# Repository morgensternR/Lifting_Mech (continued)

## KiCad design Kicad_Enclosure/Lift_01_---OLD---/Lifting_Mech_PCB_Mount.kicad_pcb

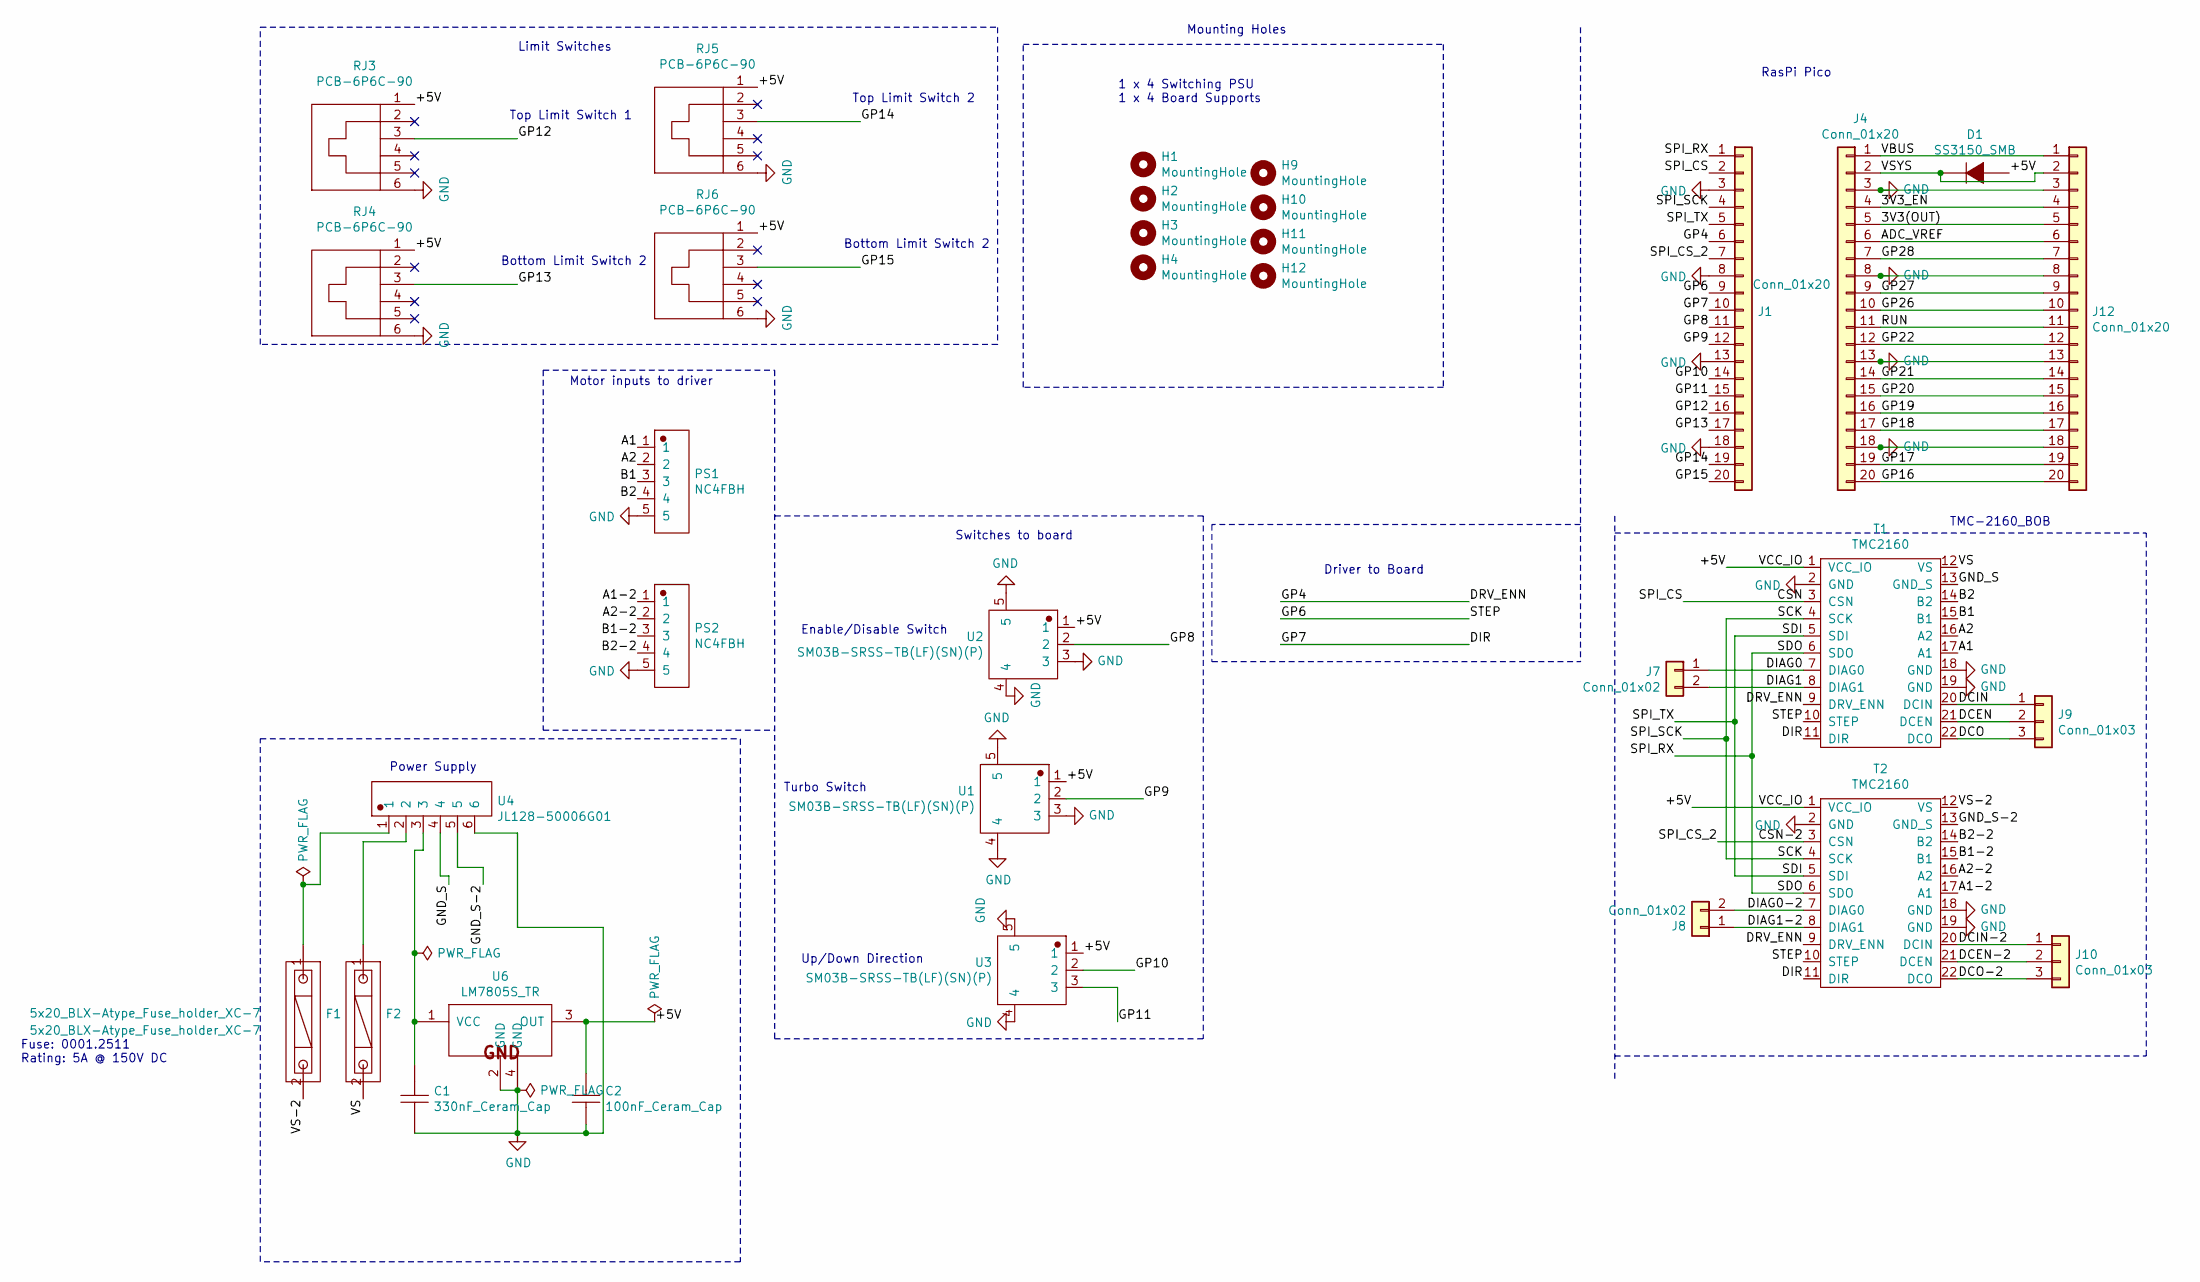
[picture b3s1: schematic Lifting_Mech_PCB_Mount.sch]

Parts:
C1: 330nF_Ceram_Cap; C1206-330nF; LCSC C710478
C2: 100nF_Ceram_Cap; C0805-100nF; LCSC C28233
D1: SS3150_SMB; SMB_L4.6-W3.6_Schottky; LCSC C47124
F1, F2: 5x20_BLX-Atype_Fuse_holder_XC-7; FUSE-TH_L22.6-W9.0; LCSC C3131
H1, H2, H3, H4: MountingHole; MountingHole_5.3mm_M5_DIN965_Pad
H9, H10, H11, H12: MountingHole; MountingHole_3.2mm_M3_DIN965_Pad
J1, J4, J12: Conn_01x20; PinSocket_1x20_P2.54mm_Vertical; LCSC C2833318
J7, J8: Conn_01x02; PinSocket_1x02_P2.54mm_Vertical
J9, J10: Conn_01x03; PinSocket_1x03_P2.54mm_Vertical
PS1, PS2: NC4FBH; CONN-TH_NC4FBH_XLR4_Female_RA_Panel; LCSC std:240b847a4e2e4ed7980c8865ae95f7a5
RJ3, RJ4, RJ5, RJ6: PCB-6P6C-90; RJ11-TH_PCB-6P6C-90; LCSC C189750
T1, T2: TMC2160; TMC_2160
U1, U2, U3: SM03B-SRSS-TB(LF)(SN)(P); CONN-SMD_SM03B-SRSS-TB-LF-SN-P; LCSC C160403
U4: JL128-50006G01; CONN-TH_JL128-50006G01_6_Screw; LCSC C2802630
U6: LM7805S_TR; TO-263-3_L8.6-W10.2-P2.54-LS14.4-BR; LCSC C507146

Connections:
/3V3(OUT): J4.5, J12.5
/3V3_EN: J4.4, J12.4
/+5V: C2.1, D1.1 (A), RJ3.1, RJ4.1, RJ5.1, RJ6.1, T1.1 (VCC_IO), T2.1 (VCC_IO), U1.1, U2.1, U3.1, U6.3 (OUT)
/A1: PS1.1, T1.17 (A1)
/A1-2: PS2.1, T2.17 (A1)
/A2: PS1.2, T1.16 (A2)
/A2-2: PS2.2, T2.16 (A2)
/ADC_VREF: J4.6, J12.6
/B1: PS1.3, T1.15 (B1)
/B1-2: PS2.3, T2.15 (B1)
/B2: PS1.4, T1.14 (B2)
/B2-2: PS2.4, T2.14 (B2)
/CSN: J1.2, T1.3 (CSN)
/CSN-2: J1.7, T2.3 (CSN)
/DCEN: J9.2, T1.21 (DCEN)
/DCEN-2: J10.2, T2.21 (DCEN)
/DCIN: J9.1, T1.20 (DCIN)
/DCIN-2: J10.1, T2.20 (DCIN)
/DCO: J9.3, T1.22 (DCO)
/DCO-2: J10.3, T2.22 (DCO)
/DIAG0: J7.1, T1.7 (DIAG0)
/DIAG0-2: J8.2, T2.7 (DIAG0)
/DIAG1: J7.2, T1.8 (DIAG1)
/DIAG1-2: J8.1, T2.8 (DIAG1)
/DIR: J1.10, T1.11 (DIR), T2.11 (DIR)
/DRV_ENN: J1.6, T1.9 (DRV_ENN), T2.9 (DRV_ENN)
/GND_S: T1.13 (GND_S), U4.4
/GND_S-2: T2.13 (GND_S), U4.5
/GP6: J1.9, T1.10 (STEP), T2.10 (STEP)
/GP8: J1.11, U2.2
/GP9: J1.12, U1.2
/GP10: J1.14, U3.2
/GP11: J1.15, U3.3
/GP12: J1.16, RJ3.3
/GP13: J1.17, RJ4.3
/GP14: J1.19, RJ5.3
/GP15: J1.20, RJ6.3
/GP16: J4.20, J12.20
/GP17: J4.19, J12.19
/GP18: J4.17, J12.17
/GP19: J4.16, J12.16
/GP20: J4.15, J12.15
/GP21: J4.14, J12.14
/GP22: J4.12, J12.12
/GP26: J4.10, J12.10
/GP27: J4.9, J12.9
/GP28: J4.7, J12.7
/RUN: J4.11, J12.11
/SCK: J1.4, T1.4 (SCK), T2.4 (SCK)
/SDI: J1.5, T1.5 (SDI), T2.5 (SDI)
/SDO: J1.1, T1.6 (SDO), T2.6 (SDO)
/VBUS: J4.1, J12.1
/VS: F2.2, T1.12 (VS)
/VS-2: F1.2, T2.12 (VS)
/VSYS: D1.2 (K), J4.2, J12.2
GND: C1.2, C2.2, J1.3, J1.8, J1.13, J1.18, J4.3, J4.8, J4.13, J4.18, J12.3, J12.8, J12.13, J12.18, PS1.5, PS2.5, RJ3.6, RJ4.6, RJ5.6, RJ6.6, T1.2 (GND), T1.18 (GND), T1.19 (GND), T2.2 (GND), T2.18 (GND), T2.19 (GND), U1.3, U1.4, U1.5, U2.3, U2.4, U2.5, U3.4, U3.5, U4.6, U6.2 (GND), U6.4 (GND)
unnamed: C1.1, U4.3, U6.1 (VCC)
unnamed: F1.1, U4.1
unnamed: F2.1, U4.2

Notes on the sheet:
Enable/Disable Switch
Up/Down Direction
Driver to Board
Mounting Holes
Limit Switches
Top Limit Switch 1
Bottom Limit Switch 2
Top Limit Switch 2
Motor inputs to driver
TMC-2160_BOB
Turbo Switch
Switches to board
Power Supply
1 x 4 Switching PSU 1 x 4 Board Supports
RasPi Pico
Fuse: 0001.2511 Rating: 5A @ 150V DC

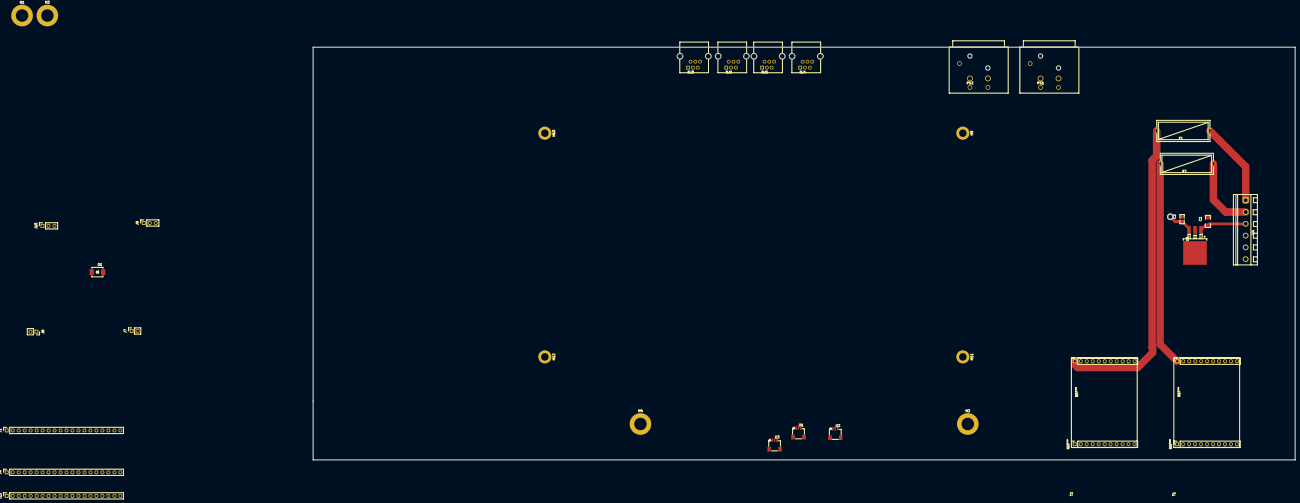
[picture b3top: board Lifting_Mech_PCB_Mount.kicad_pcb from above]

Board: 2 copper layers, 417.0 x 175.2 mm, 33 parts (0 on the bottom side), 59 nets.

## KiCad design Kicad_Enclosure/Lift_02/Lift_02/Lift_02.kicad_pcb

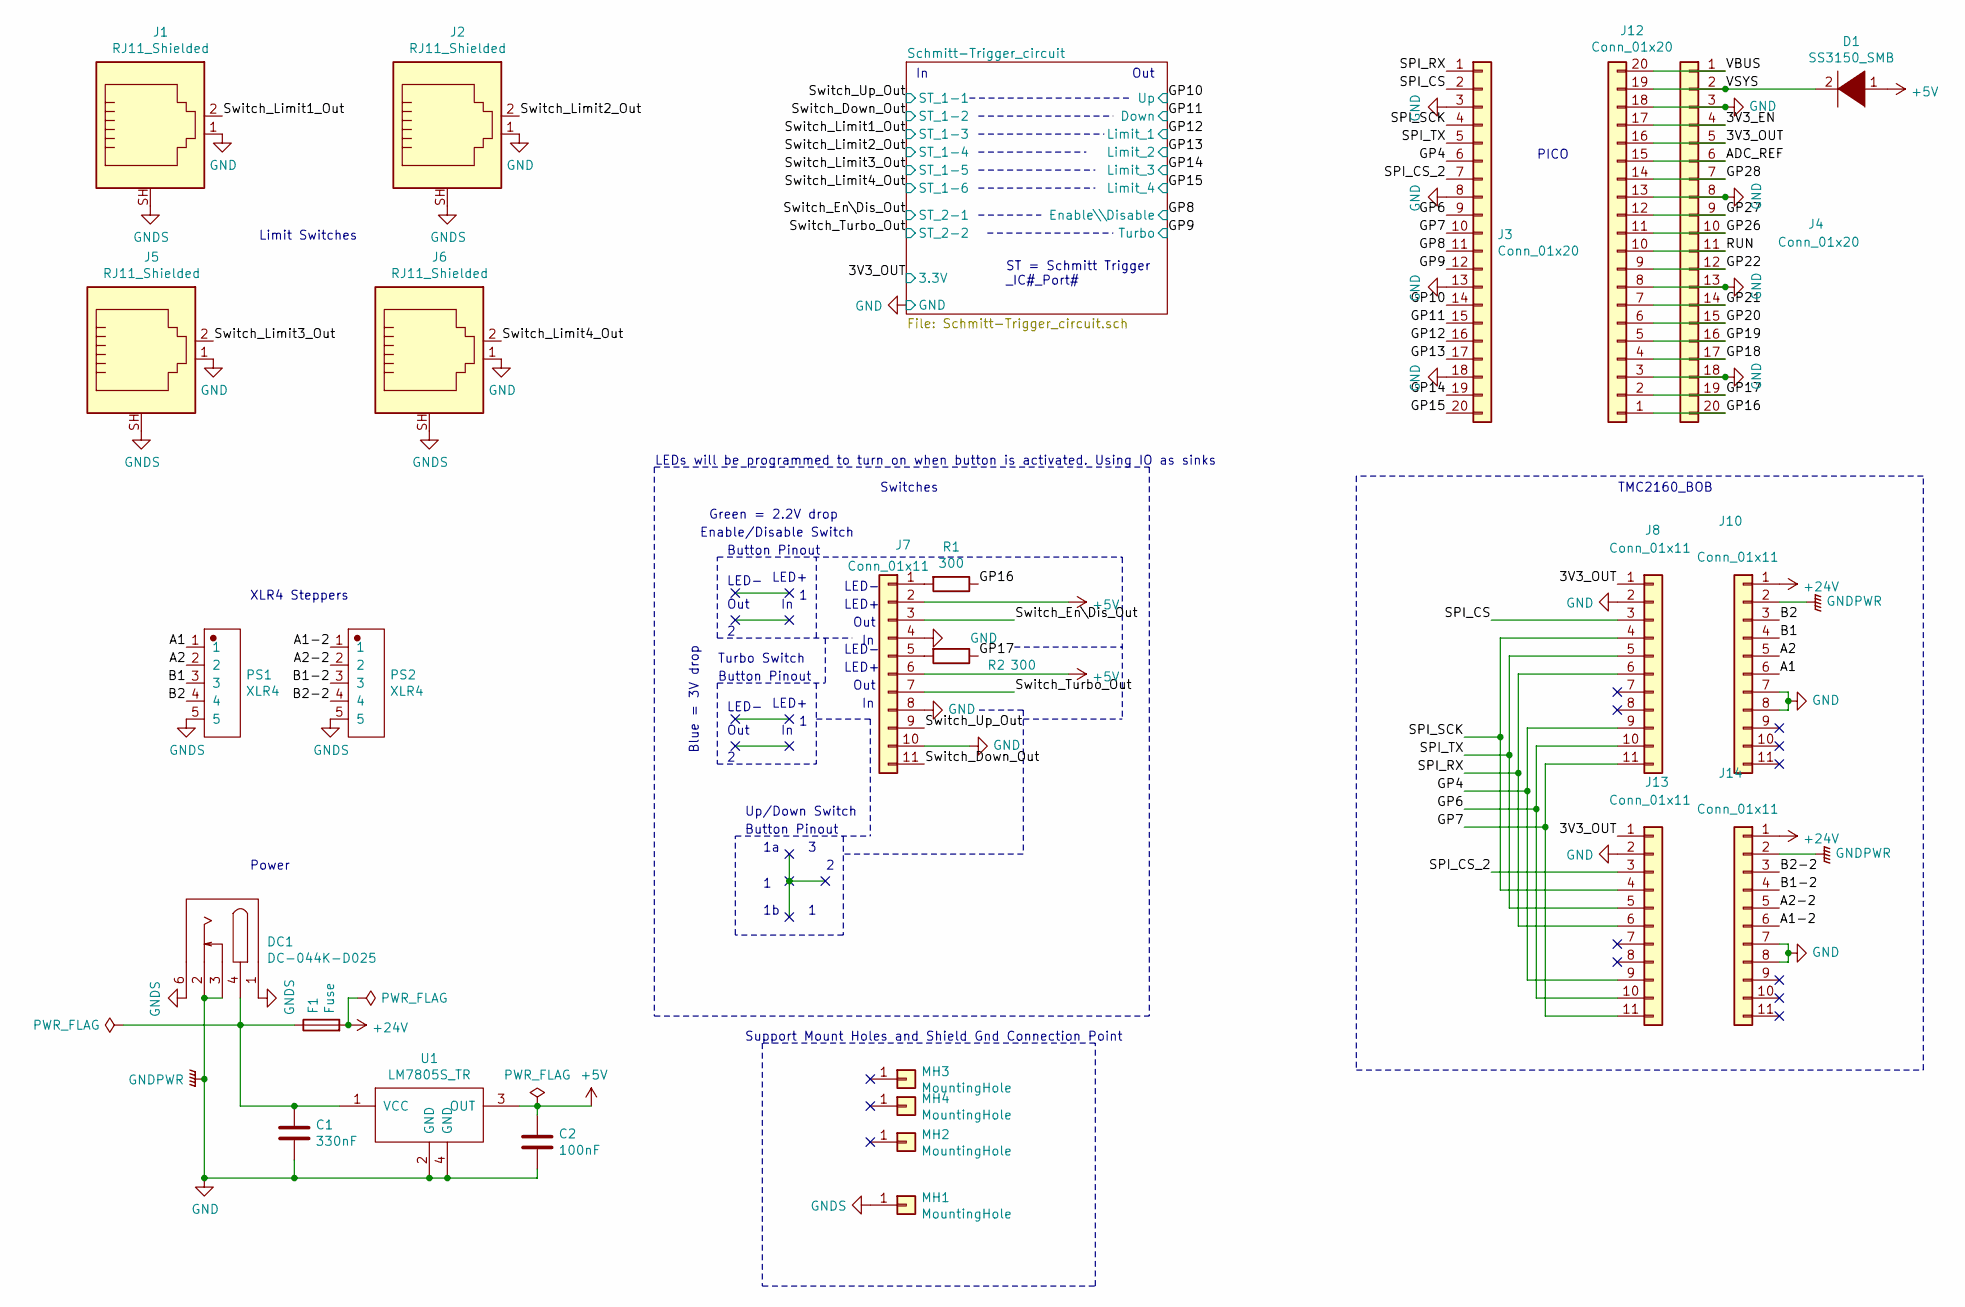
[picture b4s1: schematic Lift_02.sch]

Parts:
C1: 330nF; C_1206_3216Metric_Pad1.33x1.80mm_HandSolder; LCSC C710478
C2: 100nF; C_0805_2012Metric_Pad1.18x1.45mm_HandSolder; LCSC C28233
D1: SS3150_SMB; SMB_L4.6-W3.6-LS5.3-R-RD; LCSC C47124
DC1: DC-044K-D025; DC-IN-TH_DC-044K-D025; LCSC C963204
F1: Fuse; FUSE-TH_L22.6-W9.0; LCSC C3131
J1, J2, J5, J6: RJ11_Shielded; RJ11-TH_PCB-6P6C-90; LCSC C189750
J3, J4: Conn_01x20; PinSocket_1x20_P2.54mm_Vertical; LCSC C50984
J7: Conn_01x11; CONN-TH_B11B-ZR-LF-SN; LCSC C160345
J8, J10, J13, J14: Conn_01x11; PinSocket_1x11_P2.54mm_Vertical; LCSC C2897374
J12: Conn_01x20; PinHeader_1x20_P2.54mm_Vertical
MH1: MountingHole; MountingHole_5.3mm_M5_DIN965_Pad
MH2, MH3, MH4: MountingHole; MountingHole_5.3mm_M5
PS1, PS2: XLR4; CONN-TH_NC4FBH; LCSC C368478
R1, R2: 300; R_0805_2012Metric_Pad1.20x1.40mm_HandSolder; LCSC C17617
U1: LM7805S_TR; TO-263-3_L8.6-W10.2-P2.54-LS14.4-BR; LCSC C507146

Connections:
+5V: C2.1, D1.1 (K), J7.2, J7.6, U1.3 (OUT)
+24V: F1.2, J10.1, J14.1
/3V3_EN: J4.4, J12.17
/3V3_OUT: J4.5, J8.1, J12.16, J13.1; also elsewhere on the board
/A1: J10.6, PS1.1
/A1-2: J14.6, PS2.1
/A2: J10.5, PS1.2
/A2-2: J14.5, PS2.2
/ADC_REF: J4.6, J12.15
/B1: J10.4, PS1.3
/B1-2: J14.4, PS2.3
/B2: J10.3, PS1.4
/B2-2: J14.3, PS2.4
/GP4: J3.6, J8.9, J13.9
/GP6: J3.9, J8.10, J13.10
/GP7: J3.10, J8.11, J13.11
/GP8: J3.11; also elsewhere on the board
/GP9: J3.12; also elsewhere on the board
/GP10: J3.14; also elsewhere on the board
/GP11: J3.15; also elsewhere on the board
/GP12: J3.16; also elsewhere on the board
/GP13: J3.17; also elsewhere on the board
/GP14: J3.19; also elsewhere on the board
/GP15: J3.20; also elsewhere on the board
/GP16: J4.20, J12.1, R1.1
/GP17: J4.19, J12.2, R2.1
/GP18: J4.17, J12.4
/GP19: J4.16, J12.5
/GP20: J4.15, J12.6
/GP21: J4.14, J12.7
/GP22: J4.12, J12.9
/GP26: J4.10, J12.11
/GP27: J4.9, J12.12
/GP28: J4.7, J12.14
/RUN: J4.11, J12.10
/SPI_CS: J3.2, J8.3
/SPI_CS_2: J3.7, J13.3
/SPI_RX: J3.1, J8.6, J13.6
/SPI_SCK: J3.4, J8.4, J13.4
/SPI_TX: J3.5, J8.5, J13.5
/Switch_Down_Out: J7.11; also elsewhere on the board
/Switch_En\Dis_Out: J7.3; also elsewhere on the board
/Switch_Limit1_Out: J1.2; also elsewhere on the board
/Switch_Limit2_Out: J2.2; also elsewhere on the board
/Switch_Limit3_Out: J5.2; also elsewhere on the board
/Switch_Limit4_Out: J6.2; also elsewhere on the board
/Switch_Turbo_Out: J7.7; also elsewhere on the board
/Switch_Up_Out: J7.9; also elsewhere on the board
/VBUS: J4.1, J12.20
/VSYS: D1.2 (A), J4.2, J12.19
GND: C1.2, C2.2, DC1.2, DC1.3, J1.1, J2.1, J3.3, J3.8, J3.13, J3.18, J4.3, J4.8, J4.13, J4.18, J5.1, J6.1, J7.4, J7.8, J7.10, J8.2, J10.2, J10.7, J10.8, J12.3, J12.8, J12.13, J12.18, J13.2, J14.2, J14.7, J14.8, U1.2 (GND), U1.4 (GND); also elsewhere on the board
GNDS: DC1.1, DC1.6, J1.SH, J2.SH, J5.SH, J6.SH, MH1.1, PS1.5, PS2.5
unnamed: C1.1, DC1.4, F1.1, U1.1 (VCC)
unnamed: J7.1, R1.2
unnamed: J7.5, R2.2

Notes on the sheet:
Up/Down Switch
Enable/Disable Switch
LED+
LED-
Out
Button Pinout
Switches
Out
LED+
LED-
Turbo Switch
LEDs will be programmed to turn on when button is activated. Using IO as sinks
XLR4 Steppers
Power
Limit Switches
PICO
Support Mount Holes and Shield Gnd Connection Point
TMC2160_BOB
ST = Schmitt Trigger _IC#_Port#
Blue = 3V drop
Green = 2.2V drop

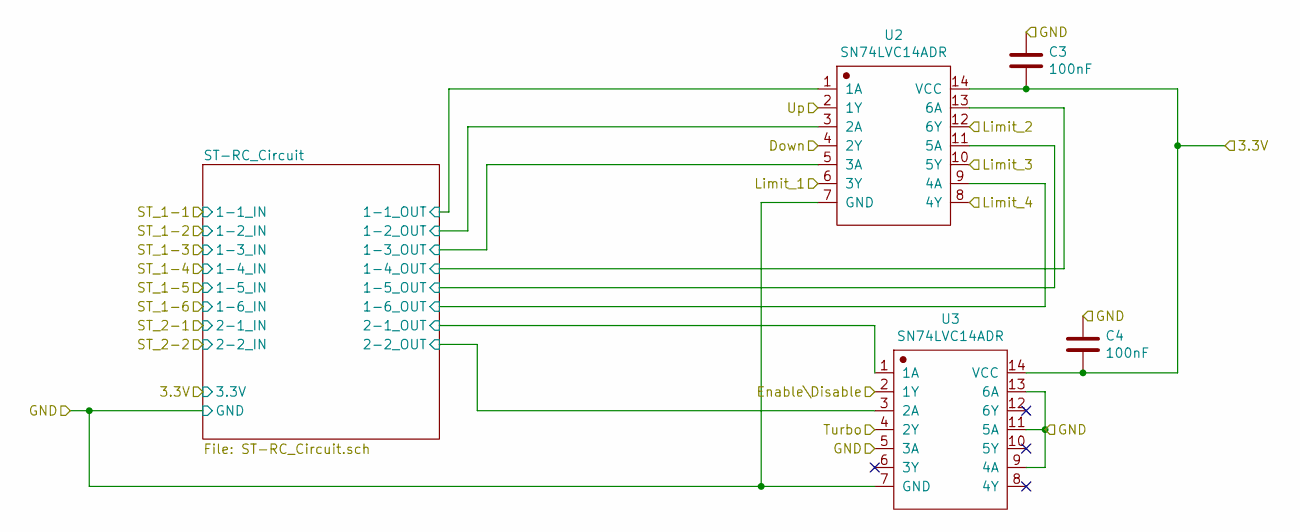
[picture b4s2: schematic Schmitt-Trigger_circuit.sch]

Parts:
C3, C4: 100nF; C_0603_1608Metric_Pad1.08x0.95mm_HandSolder; LCSC C14663
U2, U3: SN74LVC14ADR; SOIC-14_3.9x8.7mm_P1.27mm; LCSC C133541

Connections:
/3V3_OUT: C3.2, C4.2, U2.14 (VCC), U3.14 (VCC); also elsewhere on the board
/GP8: U3.2 (1Y); also elsewhere on the board
/GP9: U3.4 (2Y); also elsewhere on the board
/GP10: U2.2 (1Y); also elsewhere on the board
/GP11: U2.4 (2Y); also elsewhere on the board
/GP12: U2.6 (3Y); also elsewhere on the board
/GP13: U2.12 (6Y); also elsewhere on the board
/GP14: U2.10 (5Y); also elsewhere on the board
/GP15: U2.8 (4Y); also elsewhere on the board
/Schmitt-Trigger_circuit/ST-RC_Circuit/1-1_OUT: U2.1 (1A); also elsewhere on the board
/Schmitt-Trigger_circuit/ST-RC_Circuit/1-2_OUT: U2.3 (2A); also elsewhere on the board
/Schmitt-Trigger_circuit/ST-RC_Circuit/1-3_OUT: U2.5 (3A); also elsewhere on the board
/Schmitt-Trigger_circuit/ST-RC_Circuit/1-4_OUT: U2.13 (6A); also elsewhere on the board
/Schmitt-Trigger_circuit/ST-RC_Circuit/1-5_OUT: U2.11 (5A); also elsewhere on the board
/Schmitt-Trigger_circuit/ST-RC_Circuit/1-6_OUT: U2.9 (4A); also elsewhere on the board
/Schmitt-Trigger_circuit/ST-RC_Circuit/2-1_OUT: U3.1 (1A); also elsewhere on the board
/Schmitt-Trigger_circuit/ST-RC_Circuit/2-2_OUT: U3.3 (2A); also elsewhere on the board
GND: C3.1, C4.1, U2.7 (GND), U3.5 (3A), U3.7 (GND), U3.9 (4A), U3.11 (5A), U3.13 (6A); also elsewhere on the board

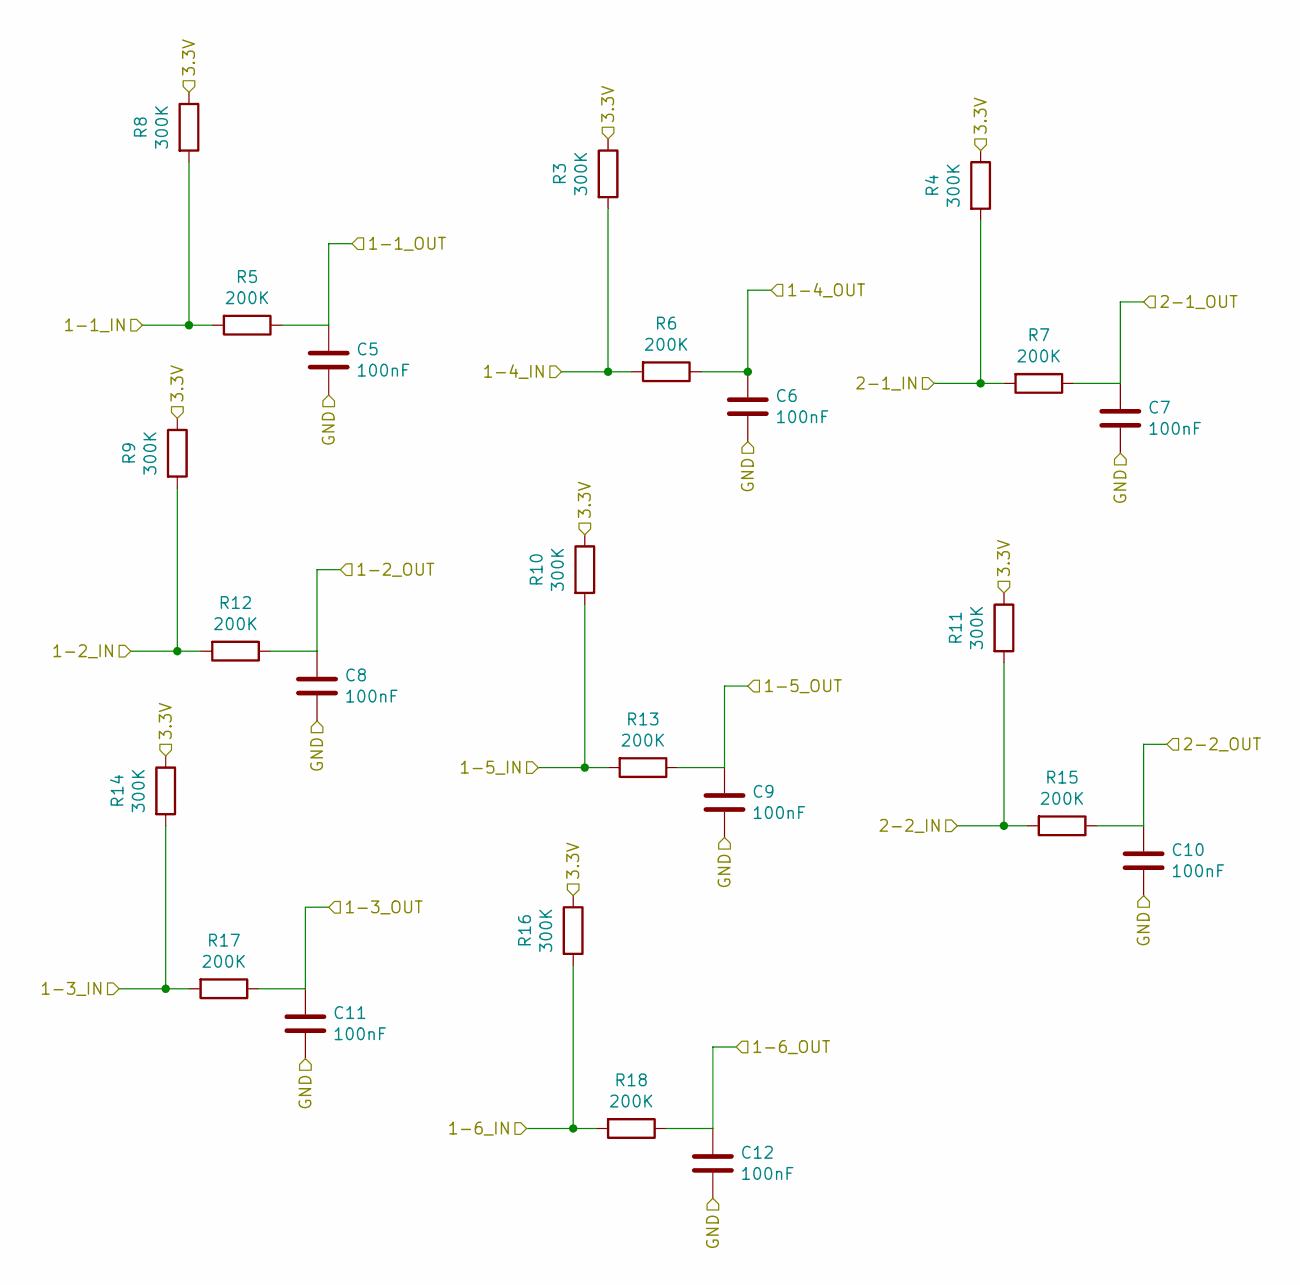
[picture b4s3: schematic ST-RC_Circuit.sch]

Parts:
C5, C6, C7, C8, C9, C10, C11, C12: 100nF; C_0603_1608Metric_Pad1.08x0.95mm_HandSolder; LCSC C14663
R3, R4, R8, R9, R10, R11, R14, R16: 300K; R_0603_1608Metric_Pad0.98x0.95mm_HandSolder; LCSC C23024
R5, R6, R7, R12, R13, R15, R17, R18: 200K; R_0603_1608Metric_Pad0.98x0.95mm_HandSolder; LCSC C25811

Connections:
/3V3_OUT: R3.1, R4.1, R8.1, R9.1, R10.1, R11.1, R14.1, R16.1; also elsewhere on the board
/Schmitt-Trigger_circuit/ST-RC_Circuit/1-1_OUT: C5.1, R5.1; also elsewhere on the board
/Schmitt-Trigger_circuit/ST-RC_Circuit/1-2_OUT: C8.1, R12.1; also elsewhere on the board
/Schmitt-Trigger_circuit/ST-RC_Circuit/1-3_OUT: C11.1, R17.1; also elsewhere on the board
/Schmitt-Trigger_circuit/ST-RC_Circuit/1-4_OUT: C6.1, R6.1; also elsewhere on the board
/Schmitt-Trigger_circuit/ST-RC_Circuit/1-5_OUT: C9.1, R13.1; also elsewhere on the board
/Schmitt-Trigger_circuit/ST-RC_Circuit/1-6_OUT: C12.1, R18.1; also elsewhere on the board
/Schmitt-Trigger_circuit/ST-RC_Circuit/2-1_OUT: C7.1, R7.1; also elsewhere on the board
/Schmitt-Trigger_circuit/ST-RC_Circuit/2-2_OUT: C10.1, R15.1; also elsewhere on the board
/Switch_Down_Out: R9.2, R12.2; also elsewhere on the board
/Switch_En\Dis_Out: R4.2, R7.2; also elsewhere on the board
/Switch_Limit1_Out: R14.2, R17.2; also elsewhere on the board
/Switch_Limit2_Out: R3.2, R6.2; also elsewhere on the board
/Switch_Limit3_Out: R10.2, R13.2; also elsewhere on the board
/Switch_Limit4_Out: R16.2, R18.2; also elsewhere on the board
/Switch_Turbo_Out: R11.2, R15.2; also elsewhere on the board
/Switch_Up_Out: R5.2, R8.2; also elsewhere on the board
GND: C5.2, C6.2, C7.2, C8.2, C9.2, C10.2, C11.2, C12.2; also elsewhere on the board

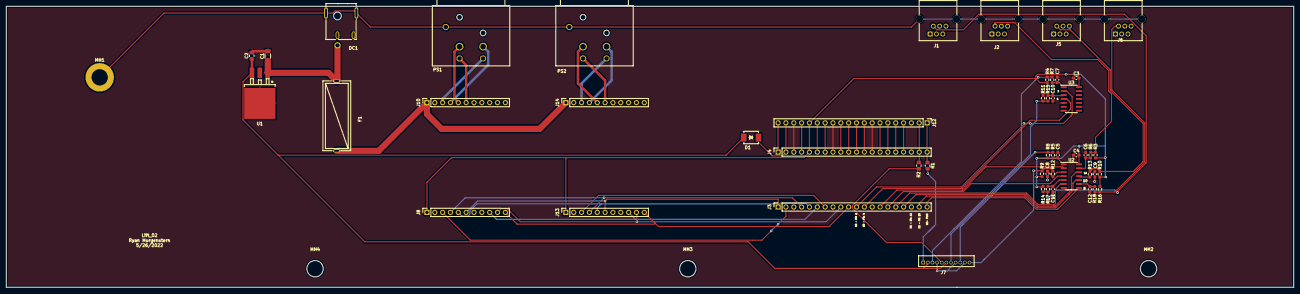
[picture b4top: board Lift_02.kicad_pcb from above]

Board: 2 copper layers, 417.0 x 91.0 mm, 54 parts (0 on the bottom side), 63 nets.

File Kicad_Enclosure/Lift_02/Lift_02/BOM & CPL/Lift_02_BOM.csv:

Comment,Designator,Footprint,LCSC
"330nF","C1","Capacitor_SMD:C_1206_3216Metric_Pad1.33x1.80mm_HandSolder","C710478"
"100nF","C2","Capacitor_SMD:C_0805_2012Metric_Pad1.18x1.45mm_HandSolder","C28233"
"100nF","C3,C4,C5,C6,C7,C8,C9,C10,C11,C12","Capacitor_SMD:C_0603_1608Metric_Pad1.08x0.95mm_HandSolder","C14663"
"SS3150_SMB","D1","0_Lift_02:SMB_L4.6-W3.6-LS5.3-R-RD","C47124"
"DC-044K-D025","DC1","0_Lift_02:DC-IN-TH_DC-044K-D025","C963204"
"Fuse","F1","0_Lift_02:FUSE-TH_L22.6-W9.0","C3131"
"Conn_01x20","J12","Connector_PinHeader_2.54mm:PinHeader_1x20_P2.54mm_Vertical",""
"RJ11_Shielded","J1,J2,J5,J6","0_Lift_02:RJ11-TH_PCB-6P6C-90","C189750"
"Conn_01x20","J3,J4","Connector_PinSocket_2.54mm:PinSocket_1x20_P2.54mm_Vertical","C50984"
"Conn_01x11","J7","0_Lift_02:CONN-TH_B11B-ZR-LF-SN","C160345"
"Conn_01x11","J8,J10,J13,J14","Connector_PinSocket_2.54mm:PinSocket_1x11_P2.54mm_Vertical","C2897374"
"MountingHole","MH1","MountingHole:MountingHole_5.3mm_M5_DIN965_Pad",""
"MountingHole","MH2,MH3,MH4","MountingHole:MountingHole_5.3mm_M5",""
"XLR4","PS1,PS2","0_Lift_02:CONN-TH_NC4FBH","C368478"
"300","R1,R2","Resistor_SMD:R_0805_2012Metric_Pad1.20x1.40mm_HandSolder","C17617"
"200K","R5,R6,R7,R12,R13,R15,R17,R18","Resistor_SMD:R_0603_1608Metric_Pad0.98x0.95mm_HandSolder","C25811"
"300K","R3,R4,R8,R9,R10,R11,R14,R16","Resistor_SMD:R_0603_1608Metric_Pad0.98x0.95mm_HandSolder","C23024"
"LM7805S_TR","U1","0_Lift_02:TO-263-3_L8.6-W10.2-P2.54-LS14.4-BR","C507146"
"SN74LVC14ADR","U2,U3","Package_SO:SOIC-14_3.9x8.7mm_P1.27mm","C133541"

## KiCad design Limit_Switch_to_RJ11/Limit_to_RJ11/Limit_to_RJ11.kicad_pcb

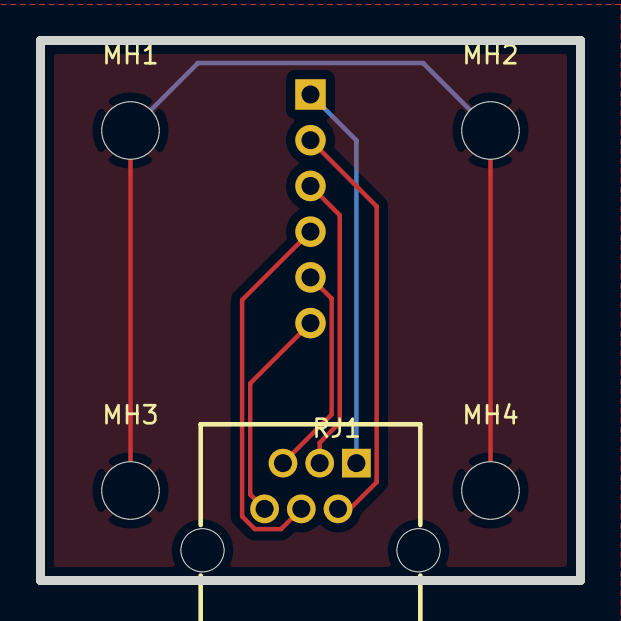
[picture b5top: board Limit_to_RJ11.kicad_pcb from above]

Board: 2 copper layers, 30.0 x 30.0 mm, 6 parts (1 on the bottom side), 7 nets.

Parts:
J1: Conn_01x06_Female; PinSocket_1x06_P2.54mm_Vertical
MH1, MH2, MH3, MH4: MountingHole; MountingHole_3.2mm_M3
RJ1: PCB-6P6C-90; RJ11-TH_PCB-6P6C-90

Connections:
GND: MH1.1, MH2.1, MH3.1, MH4.1
GNDPWR: J1.2, RJ1.2
unnamed: J1.1, RJ1.1
unnamed: J1.4, RJ1.4
unnamed: J1.5, RJ1.5
unnamed: J1.6, RJ1.6
VS: J1.3, RJ1.3
